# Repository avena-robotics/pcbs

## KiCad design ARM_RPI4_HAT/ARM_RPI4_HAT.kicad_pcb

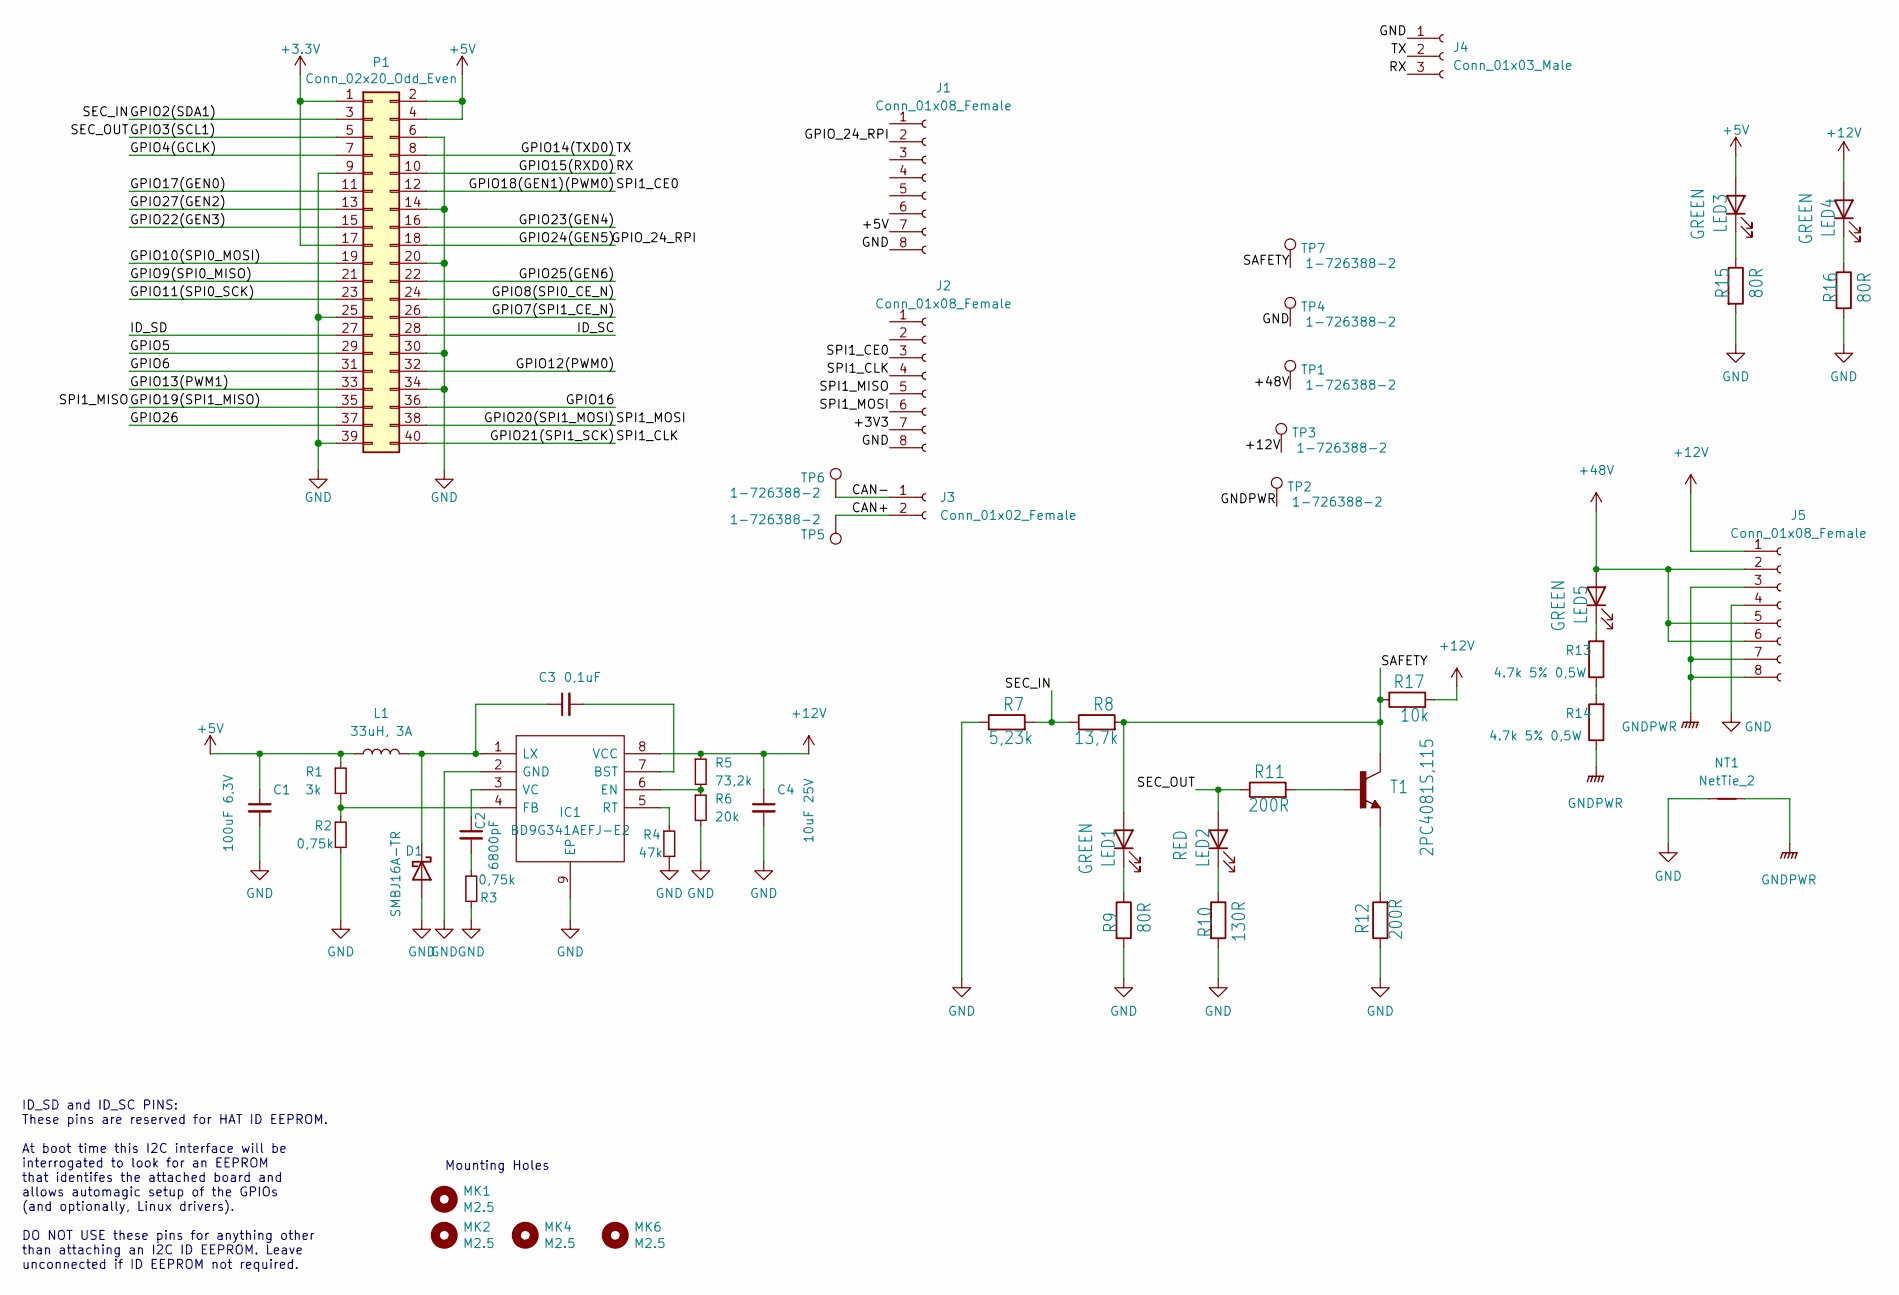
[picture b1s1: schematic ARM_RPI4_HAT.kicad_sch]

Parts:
C1: 100uF 6,3V; C_1206_3216Metric_Pad1.33x1.80mm_HandSolder
C2: 6800pF; C_0603_1608Metric_Pad1.08x0.95mm_HandSolder
C3: 0,1uF; C_0603_1608Metric_Pad1.08x0.95mm_HandSolder
C4: 10uF 25V; C_0603_1608Metric_Pad1.08x0.95mm_HandSolder
D1: SMBJ16A-TR; D_SMB_Handsoldering
IC1: BD9G341AEFJ-E2; SOIC127P600X100-9N; Mouser Part Number 755-BD9G341AEFJ-E2
J1, J2: Conn_01x08_Female; PinSocket_1x08_P2.54mm_Vertical
J3: Conn_01x02_Female; PinHeader_1x02_P2.54mm_Vertical
J4: Conn_01x03_Male; PinHeader_1x03_P2.54mm_Horizontal
J5: Conn_01x08_Female; 105314-2208
L1: 33uH, 3A; MPEV1D1040L330
LED1, LED3, LED4, LED5: GREEN; D_0603_1608Metric_Pad1.05x0.95mm_HandSolder
LED2: RED; D_0603_1608Metric_Pad1.05x0.95mm_HandSolder
MK1, MK2, MK4, MK6: M2.5; MountingHole_2.7mm_M2.5
NT1: NetTie_2; NetTie-2_SMD_Pad0.5mm
P1: Conn_02x20_Odd_Even; PinSocket_2x20_P2.54mm_Vertical
R1: 3k; R_0603_1608Metric_Pad0.98x0.95mm_HandSolder
R2, R3: 0,75k; R_0603_1608Metric_Pad0.98x0.95mm_HandSolder
R4: 47k; R_0603_1608Metric_Pad0.98x0.95mm_HandSolder
R5: 73,2k; R_0603_1608Metric_Pad0.98x0.95mm_HandSolder
R6: 20k; R_0603_1608Metric_Pad0.98x0.95mm_HandSolder
R7: 5,23k; R_0603_1608Metric_Pad0.98x0.95mm_HandSolder
R8: 13,7k; R_0603_1608Metric_Pad0.98x0.95mm_HandSolder
R9, R15, R16: 80R; R_0603_1608Metric_Pad0.98x0.95mm_HandSolder
R10: 130R; R_0603_1608Metric_Pad0.98x0.95mm_HandSolder
R11, R12: 200R; R_0603_1608Metric_Pad0.98x0.95mm_HandSolder
R13, R14: 4.7k 5% 0,5W; R_0805_2012Metric_Pad1.20x1.40mm_HandSolder
R17: 10k; R_0603_1608Metric_Pad0.98x0.95mm_HandSolder
T1: 2PC4081S,115; SOT23-EBC
TP1, TP2: 1-726388-2; 61-1537-11-0031
TP3, TP4, TP5, TP6, TP7: 1-726388-2; 61-1407-21-0031

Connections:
+5V: C1.1, J1.7, L1.1, LED3.2 (A), P1.2, P1.4, R1.1
+12V: C4.1, IC1.8 (VCC), J5.1, LED4.2 (A), R5.1, R17.2, TP3.1
+48V: J5.2, J5.5, J5.6, LED5.2 (A), TP1.1
/CAN+: J3.2, TP5.1
/CAN-: J3.1, TP6.1
/GPIO2(SDA1): P1.3, R7.2, R8.1
/GPIO3(SCL1): LED2.2 (A), P1.5, R11.1
/GPIO4(GCLK): P1.7
/GPIO5: P1.29
/GPIO6: P1.31
/GPIO7(SPI1_CE_N): P1.26
/GPIO8(SPI0_CE_N): P1.24
/GPIO9(SPI0_MISO): P1.21
/GPIO10(SPI0_MOSI): P1.19
/GPIO11(SPI0_SCK): P1.23
/GPIO12(PWM0): P1.32
/GPIO13(PWM1): P1.33
/GPIO14(TXD0): J4.2, P1.8
/GPIO15(RXD0): J4.3, P1.10
/GPIO16: P1.36
/GPIO17(GEN0): P1.11
/GPIO18(GEN1)(PWM0): J2.3, P1.12
/GPIO19(SPI1_MISO): J2.5, P1.35
/GPIO20(SPI1_MOSI): J2.6, P1.38
/GPIO21(SPI1_SCK): J2.4, P1.40
/GPIO22(GEN3): P1.15
/GPIO23(GEN4): P1.16
/GPIO24(GEN5): J1.2, P1.18
/GPIO25(GEN6): P1.22
/GPIO26: P1.37
/GPIO27(GEN2): P1.13
/ID_SC: P1.28
/ID_SD: P1.27
/SAFETY: LED1.2 (A), R8.2, R17.1, T1.C, TP7.1
GND: C1.2, C4.2, D1.2 (A), IC1.2 (GND), IC1.9 (EP), J1.8, J2.8, J4.1, J5.4, NT1.1, P1.6, P1.9, P1.14, P1.20, P1.25, P1.30, P1.34, P1.39, R2.2, R3.1, R4.2, R6.2, R7.1, R9.2, R10.2, R12.1, R15.2, R16.2, TP4.1
GNDPWR: J5.3, J5.7, J5.8, NT1.2, R14.1, TP2.1
unnamed: C2.1, IC1.3 (VC)
unnamed: C2.2, R3.2
unnamed: C3.1, D1.1 (K), IC1.1 (LX), L1.2
unnamed: C3.2, IC1.7 (BST)
unnamed: IC1.4 (FB), R1.2, R2.1
unnamed: IC1.5 (RT), R4.1
unnamed: IC1.6 (EN), R5.2, R6.1
unnamed: LED1.1 (K), R9.1
unnamed: LED2.1 (K), R10.1
unnamed: LED3.1 (K), R15.1
unnamed: LED4.1 (K), R16.1
unnamed: LED5.1 (K), R13.2
unnamed: R11.2, T1.B
unnamed: R12.2, T1.E
unnamed: R13.1, R14.2

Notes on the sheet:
ID_SD and ID_SC PINS: These pins are reserved for HAT ID EEPROM. At boot time this I2C interface will be interrogated to look for an EEPROM that identifes the attached board and allows automagic setup of the GPIOs (and optionally, Linux drivers). DO NOT USE these pins for anything other than attach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
Mounting Holes

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
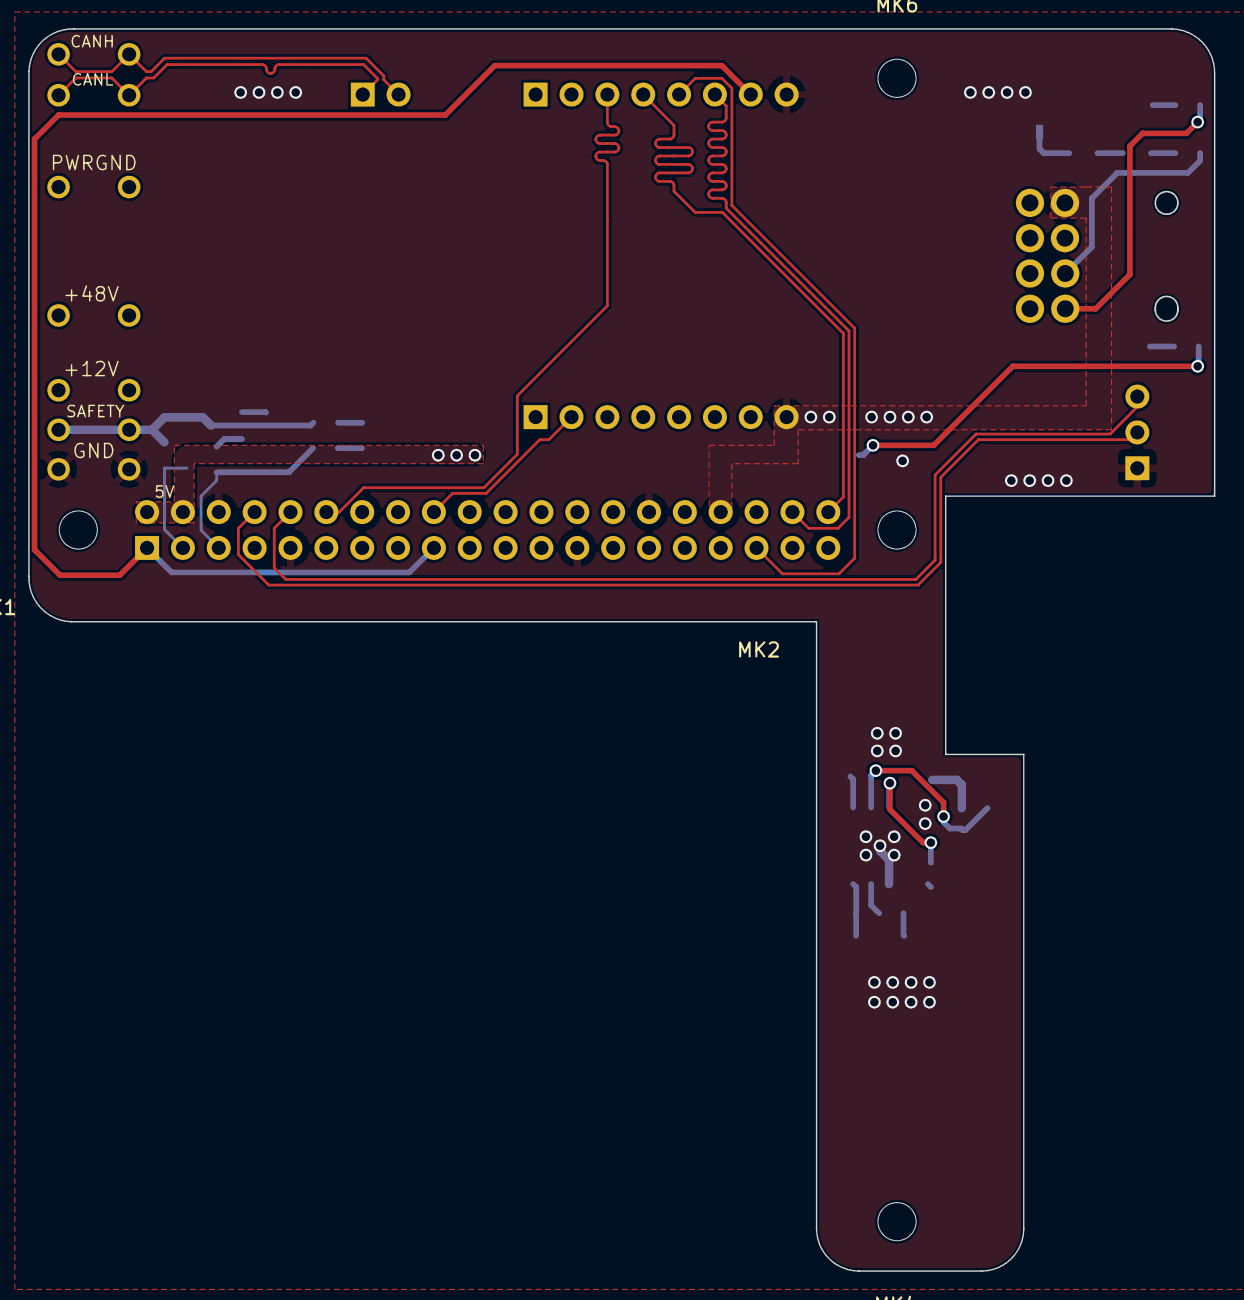
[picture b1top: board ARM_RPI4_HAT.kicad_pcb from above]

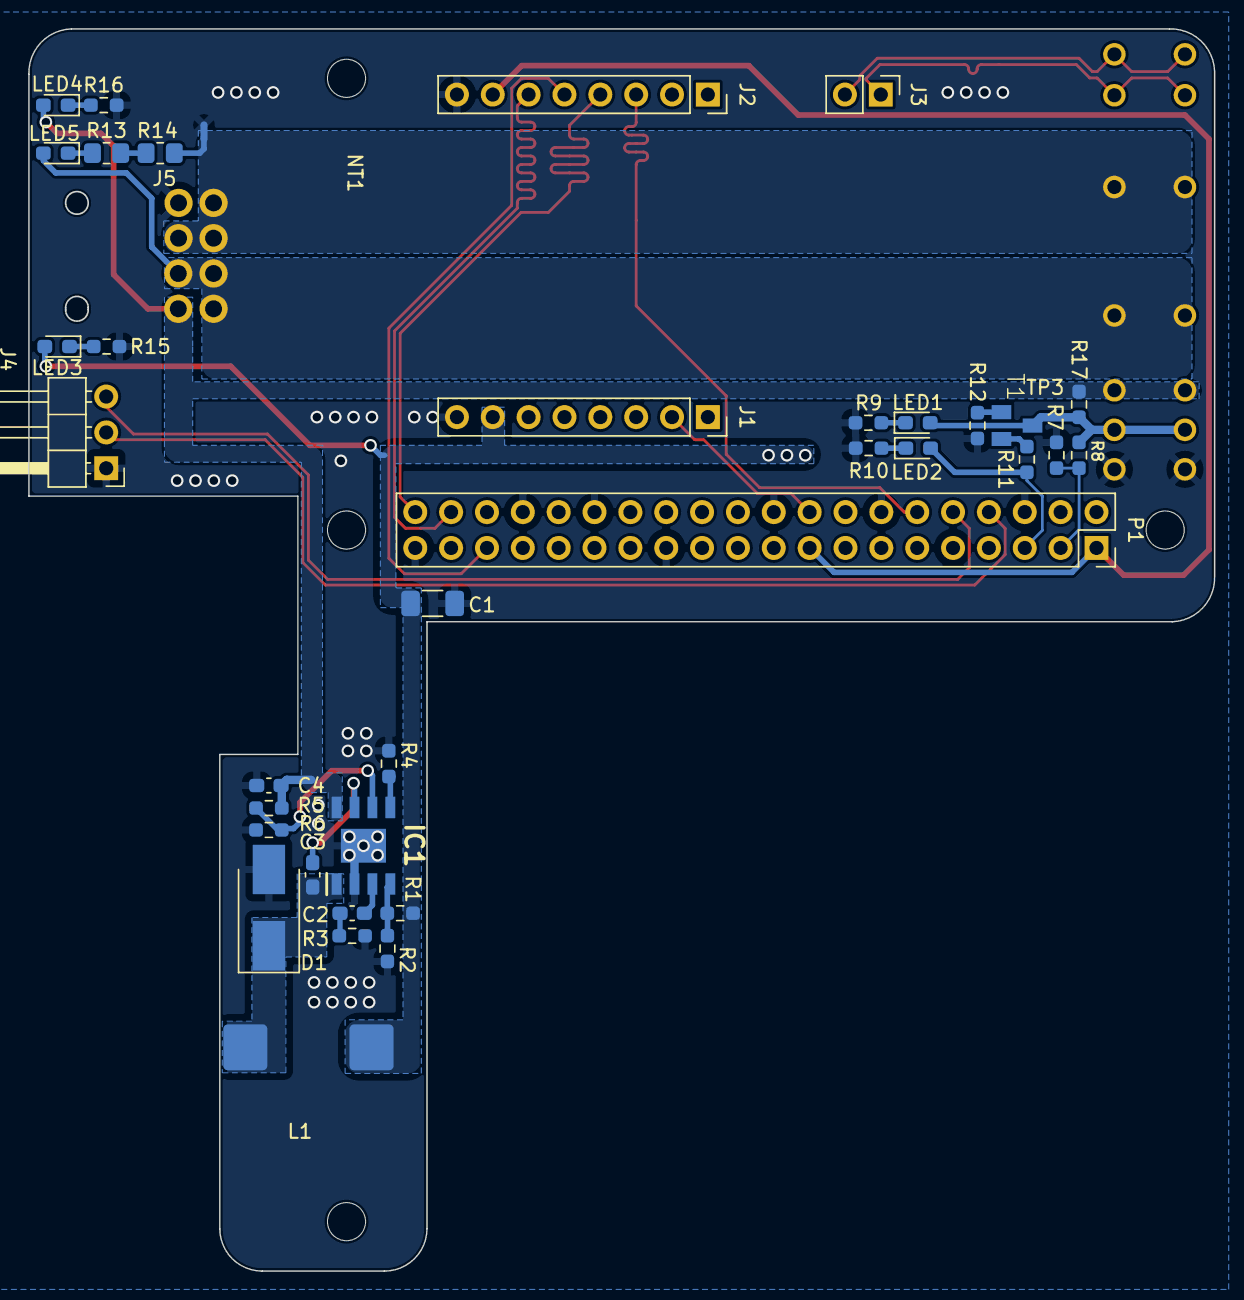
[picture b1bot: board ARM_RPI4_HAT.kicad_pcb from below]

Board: 2 copper layers, 84.0 x 88.0 mm, 48 parts (44 on the bottom side), 33 nets.

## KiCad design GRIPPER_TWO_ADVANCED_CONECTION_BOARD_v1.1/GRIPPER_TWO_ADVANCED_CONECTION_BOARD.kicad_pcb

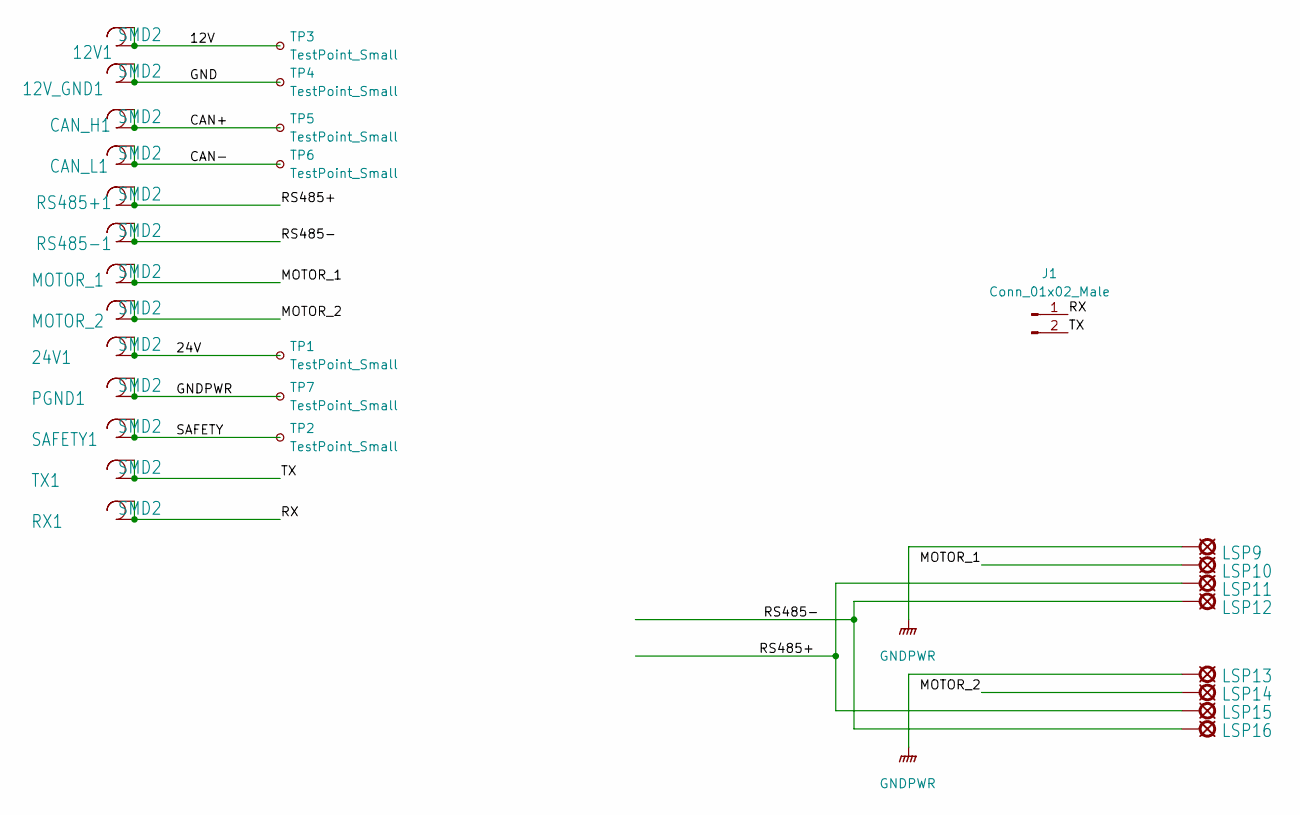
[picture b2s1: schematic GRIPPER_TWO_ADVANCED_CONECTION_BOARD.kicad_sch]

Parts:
12V1, 12V_GND1, 24V1: SMD2; SMD1,27-2,54
CAN_H1: SMD2; SMD1,27-2,54
CAN_L1: SMD2; SMD1,27-2,54
J1: Conn_01x02_Male; PinHeader_1x02_P2.54mm_Vertical
LSP9, LSP10, LSP11, LSP12, LSP13, LSP14, LSP15, LSP16: SE11
MOTOR_1, MOTOR_2: SMD2; SMD1,27-2,54
PGND1: SMD2; SMD1,27-2,54
RS485+1, RS485-1: SMD2; SMD1,27-2,54
RX1: SMD2; SMD1,27-2,54
SAFETY1: SMD2; SMD1,27-2,54
TP1, TP2, TP3, TP4, TP5, TP6, TP7: TestPoint_Small; TestPoint_Pad_1.0x1.0mm
TX1: SMD2; SMD1,27-2,54

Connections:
/12V: 12V1.1, 12V1.2, TP3.1
/24V: 24V1.1, 24V1.2, TP1.1
/CAN+: CAN_H1.1, CAN_H1.2, TP5.1
/CAN-: CAN_L1.1, CAN_L1.2, TP6.1
/GND: 12V_GND1.1, 12V_GND1.2, TP4.1
/MOTOR_1: LSP10.MP, MOTOR_1.1, MOTOR_1.2
/MOTOR_2: LSP14.MP, MOTOR_2.1, MOTOR_2.2
/RS485+: LSP11.MP, LSP15.MP, RS485+1.1, RS485+1.2
/RS485-: LSP12.MP, LSP16.MP, RS485-1.1, RS485-1.2
/RX: J1.1, RX1.1, RX1.2
/SAFETY: SAFETY1.1, SAFETY1.2, TP2.1
/TX: J1.2, TX1.1, TX1.2
GNDPWR: LSP9.MP, LSP13.MP, PGND1.1, PGND1.2, TP7.1

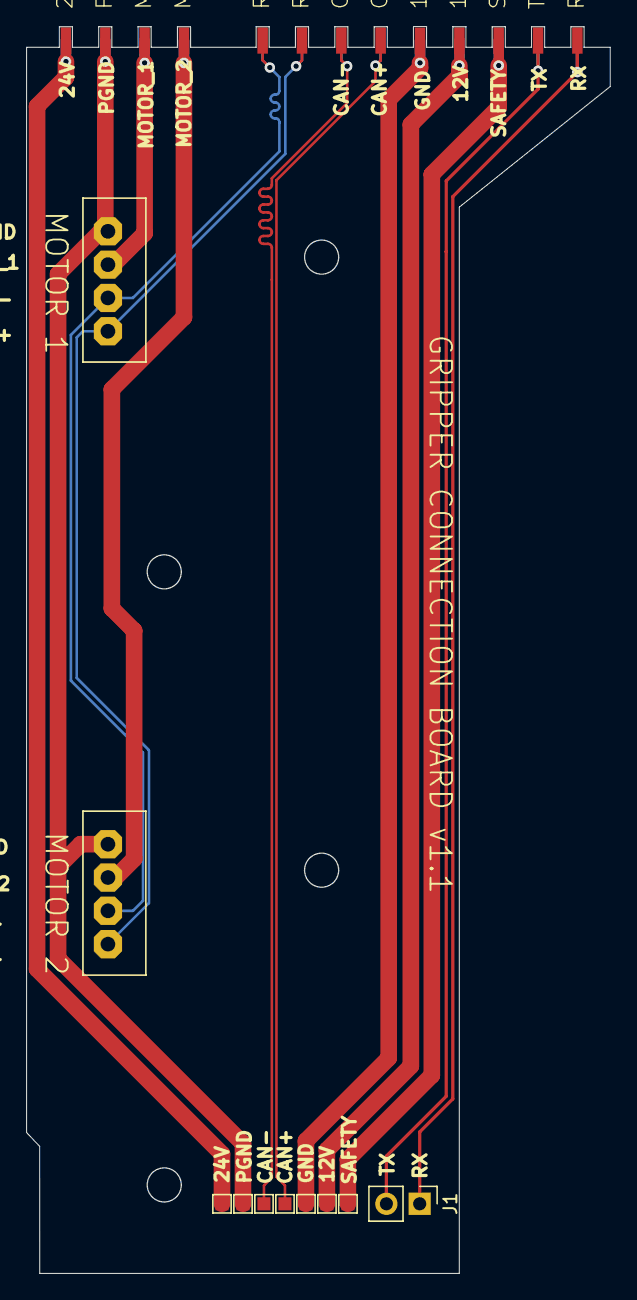
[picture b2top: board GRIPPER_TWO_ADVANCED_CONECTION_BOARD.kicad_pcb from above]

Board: 2 copper layers, 44.5 x 95.1 mm, 29 parts (0 on the bottom side), 13 nets.

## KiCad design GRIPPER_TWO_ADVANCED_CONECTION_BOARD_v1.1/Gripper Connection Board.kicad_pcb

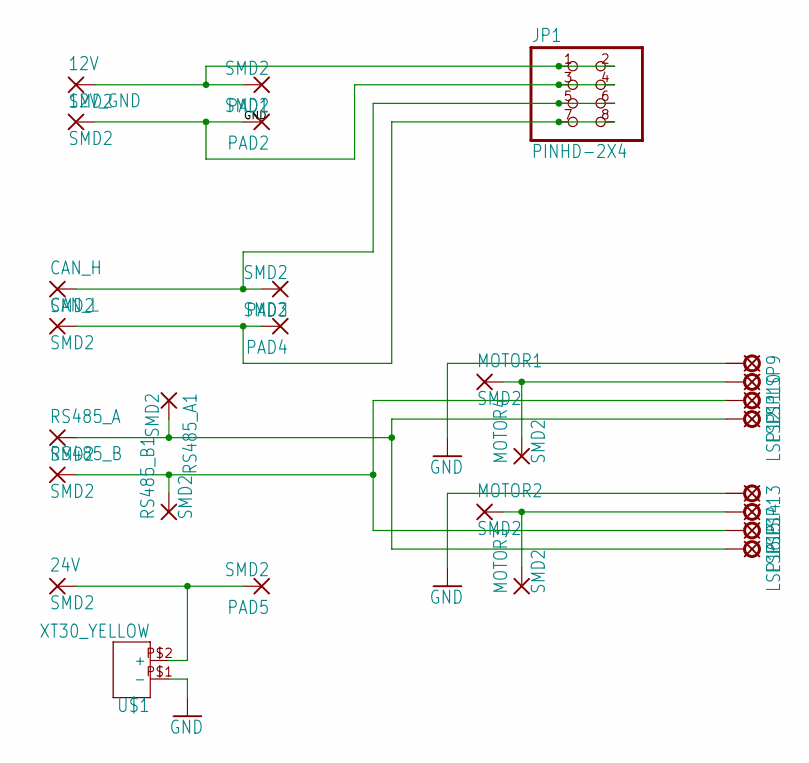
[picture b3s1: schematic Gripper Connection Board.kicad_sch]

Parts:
12V, 12V_GND, 24V: SMD2; SMD1,27-2,54
CAN_H: SMD2; SMD1,27-2,54
CAN_L: SMD2; SMD1,27-2,54
JP1: PINHD-2X4; 2X04
LSP9, LSP10, LSP11, LSP12, LSP13, LSP14, LSP15, LSP16: SE11
MOTOR1, MOTOR2, MOTOR3, MOTOR4: SMD2; SMD1,27-2,54
PAD1, PAD2, PAD3, PAD4, PAD5: SMD2; SMD1,27-2,54
RS485_A, RS485_A1, RS485_B, RS485_B1: SMD2; SMD1,27-2,54
U$1: XT30_YELLOW; XT30

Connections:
GND: 12V_GND.1, JP1.3, JP1.4, LSP9.MP, LSP13.MP, PAD2.1, U$1.P$1 (-)
unnamed: CAN_H.1, JP1.5, JP1.6, PAD3.1
unnamed: CAN_L.1, JP1.7, JP1.8, PAD4.1
unnamed: 12V.1, JP1.1, JP1.2, PAD1.1
unnamed: 24V.1, PAD5.1, U$1.P$2 (+)
unnamed: LSP11.MP, LSP15.MP, RS485_B.1, RS485_B1.1
unnamed: LSP12.MP, LSP16.MP, RS485_A.1, RS485_A1.1
unnamed: LSP10.MP, MOTOR1.1, MOTOR4.1
unnamed: LSP14.MP, MOTOR2.1, MOTOR3.1

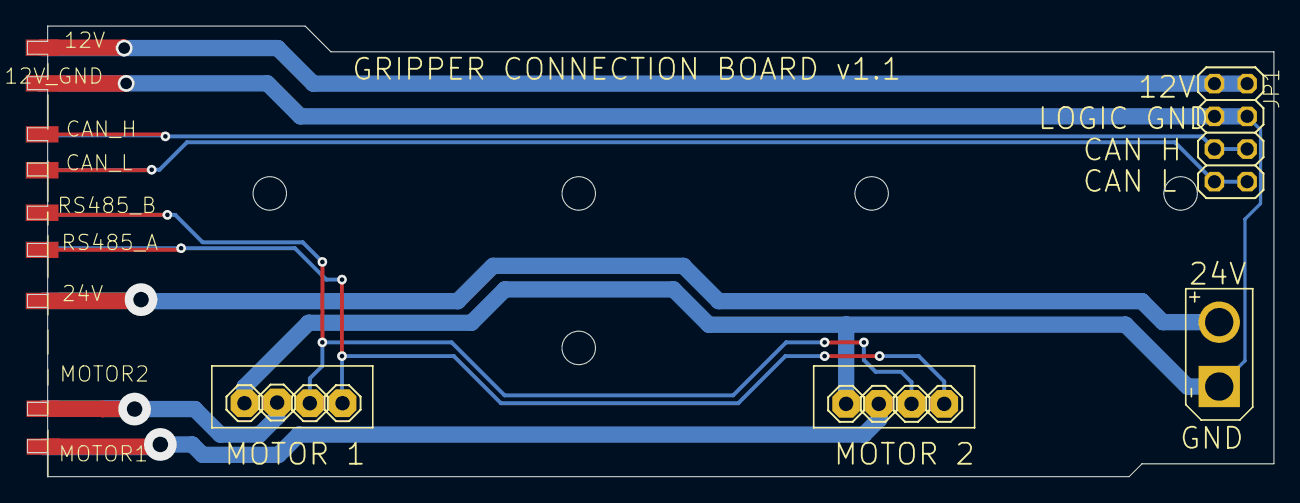
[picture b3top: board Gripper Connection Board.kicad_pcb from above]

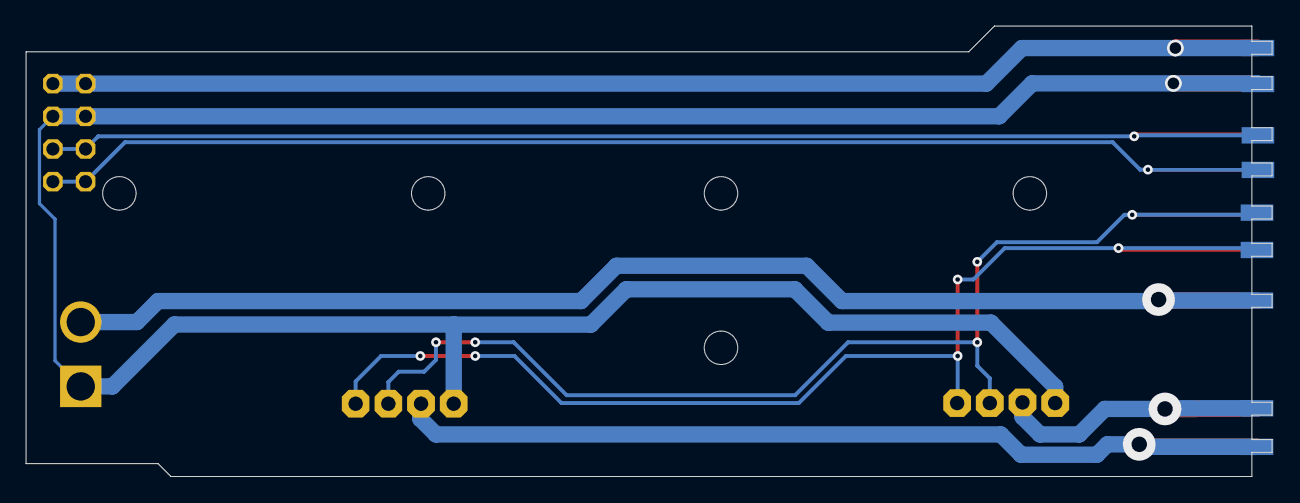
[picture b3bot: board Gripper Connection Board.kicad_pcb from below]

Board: 2 copper layers, 96.8 x 35.0 mm, 28 parts (9 on the bottom side), 9 nets.

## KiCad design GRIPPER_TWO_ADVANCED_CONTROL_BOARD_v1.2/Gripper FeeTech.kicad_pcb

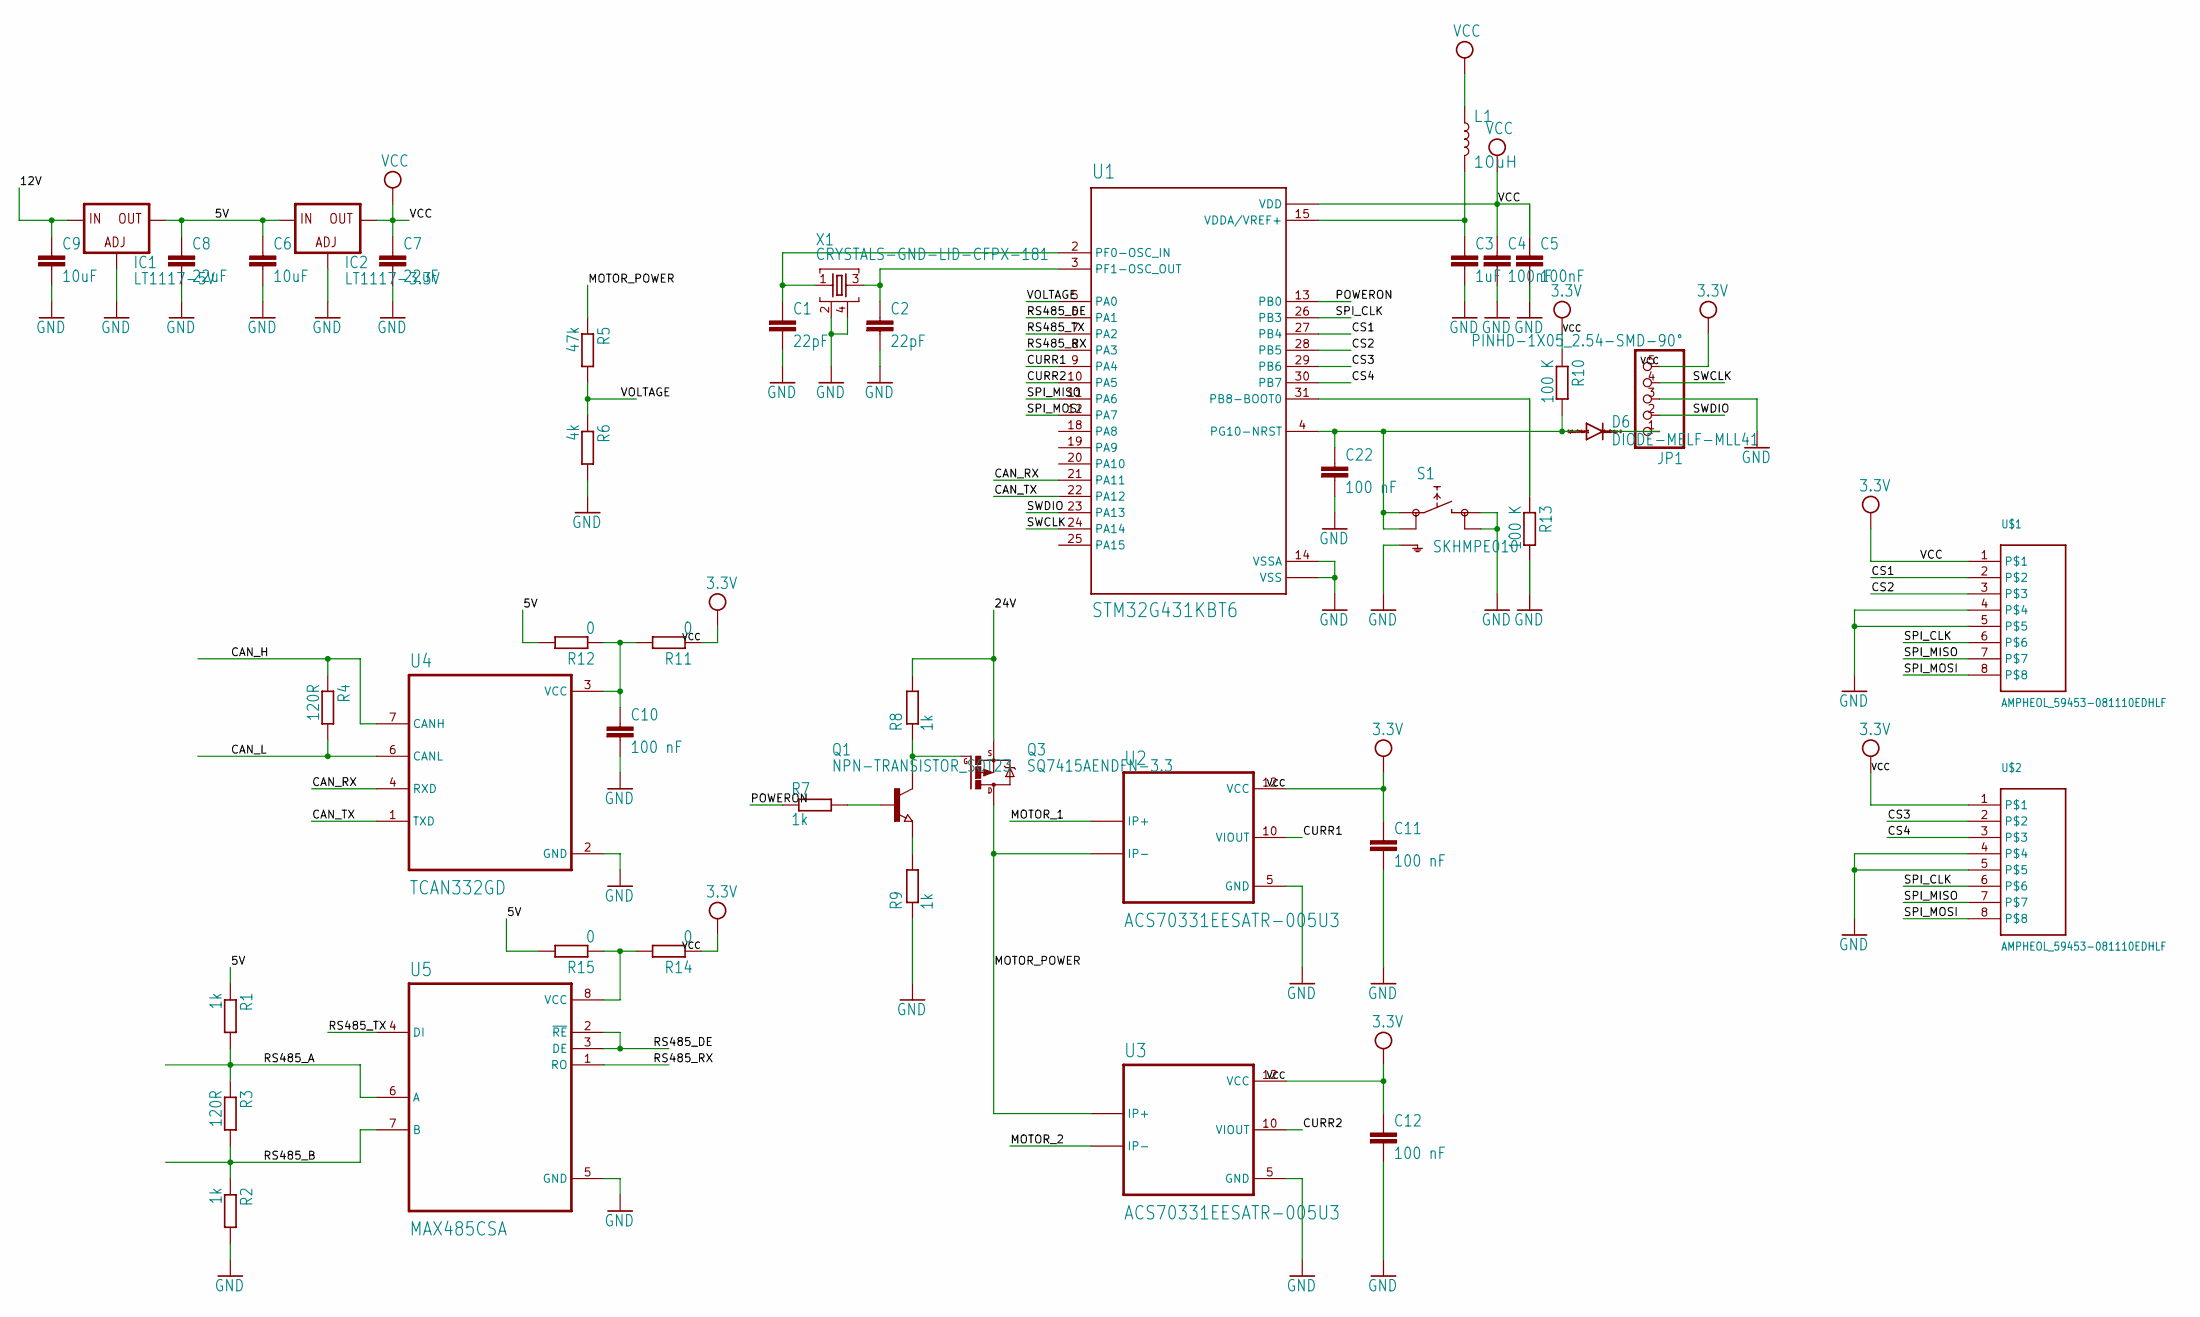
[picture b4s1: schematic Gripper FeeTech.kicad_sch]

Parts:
C1, C2: 22pF; C0402
C3: 1uF; C0402
C4, C5: 100nF; C0402
C6, C9: 10uF; C0402
C7, C8: 22uF; C0402
C10, C11, C12, C22: 100 nF; C0402
D6: DIODE-MELF-MLL41; MELF-MLL41
IC1: LT1117-5V; SOT223
IC2: LT1117-3.3V; SOT223
JP1: PINHD-1X05_2.54-SMD-90°; 1X05SMD_90
L1: 10uH; 0603
Q1: NPN-TRANSISTOR_SOT23; SOT23
Q3: SQ7415AENDFN-3.3; DFN3.3X3.3
R1, R2, R7, R8, R9: 1k; R0402
R3, R4: 120R; R0402
R5: 47k; R0402
R6: 4k; R0402
R10, R13: 100 K; R0402
R11, R12, R14, R15: 0; R0402
S1: SKHMPE010; SKHMPXE010
U1: STM32G431KBT6; QFP80P900X900X160-32N
U2, U3: ACS70331EESATR-005U3; ALLEGRO_ACS70331EESATR-005U3
U4: TCAN332GD; SOIC127P599X175-8N
U5: MAX485CSA; SOIC127P600X175-8N
U$1, U$2: AMPHEOL_59453-081110EDHLF; AMPHENOL_59453_8PIN
X1: CRYSTALS-GND-LID-CFPX-181; 2.5X2-4-PAD

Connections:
5V: C6.1, C8.1, IC1.4 (OUT), IC2.3 (IN), R1.1, R12.2, R15.2
12V: C9.1, IC1.3 (IN)
24V: Q3.1 (S), Q3.2 (S), Q3.3 (S), R8.2
CAN_H: R4.1, U4.7 (CANH)
CAN_L: R4.2, U4.6 (CANL)
CAN_RX: U1.21 (PA11), U4.4 (RXD)
CAN_TX: U1.22 (PA12), U4.1 (TXD)
CS1: U1.27 (PB4), U$1.2
CS2: U1.28 (PB5), U$1.3
CS3: U1.29 (PB6), U$2.2
CS4: U1.30 (PB7), U$2.3
CURR1: U1.9 (PA4), U2.10 (VIOUT)
CURR2: U1.10 (PA5), U3.10 (VIOUT)
GND: C1.2, C2.2, C3.2, C4.2, C5.2, C6.2, C7.2, C8.2, C9.2, C10.2, C11.2, C12.2, C22.2, IC1.1 (ADJ), IC2.1 (ADJ), JP1.3, R2.2, R6.2, R9.1, R13.2, S1.3 (2.1), S1.4 (2.2), S1.5 (SH), U1.14 (VSSA), U1.16 (VSS), U1.32 (VSS), U2.5 (GND), U3.5 (GND), U4.2 (GND), U5.5 (GND), U$1.4, U$1.5, U$2.4, U$2.5, X1.2, X1.4
MOTOR_1: U2.1 (IP+), U2.2 (IP+)
MOTOR_2: U3.3 (IP-), U3.4 (IP-)
MOTOR_POWER: Q3.5 (D), Q3.6 (D), Q3.7 (D), Q3.8 (D), R5.1, U2.3 (IP-), U2.4 (IP-), U3.1 (IP+), U3.2 (IP+)
unnamed: C2.1, U1.3 (PF1-OSC_OUT), X1.3
unnamed: C1.1, U1.2 (PF0-OSC_IN), X1.1
unnamed: C3.1, L1.2, U1.15 (VDDA/VREF+)
unnamed: C22.1, D6.A, R10.2, S1.1 (1.1), S1.2 (1.2), U1.4 (PG10-NRST)
unnamed: Q1.1 (B), R7.2
unnamed: Q1.3 (C), Q3.4 (G), R8.1
unnamed: Q1.2 (E), R9.2
unnamed: R14.2, R15.1, U5.8 (VCC)
unnamed: C10.1, R11.2, R12.1, U4.3 (VCC)
unnamed: R13.1, U1.31 (PB8-BOOT0)
POWERON: R7.1, U1.13 (PB0)
RESET: D6.C, JP1.1
RS485_A: R1.2, R3.1, U5.6 (A)
RS485_B: R2.1, R3.2, U5.7 (B)
RS485_DE: U1.6 (PA1), U5.2 (~RE), U5.3 (DE)
RS485_RX: U1.8 (PA3), U5.1 (RO)
RS485_TX: U1.7 (PA2), U5.4 (DI)
SPI_CLK: U1.26 (PB3), U$1.6, U$2.6
SPI_MISO: U1.11 (PA6), U$1.7, U$2.7
SPI_MOSI: U1.12 (PA7), U$1.8, U$2.8
SWCLK: JP1.4, U1.24 (PA14)
SWDIO: JP1.2, U1.23 (PA13)
VCC: C4.1, C5.1, C7.1, C11.1, C12.1, IC2.4 (OUT), JP1.5, L1.1, R10.1, R11.1, R14.1, U1.1 (VDD), U1.17 (VDD), U2.12 (VCC), U3.12 (VCC), U$1.1, U$2.1
VOLTAGE: R5.2, R6.1, U1.5 (PA0)

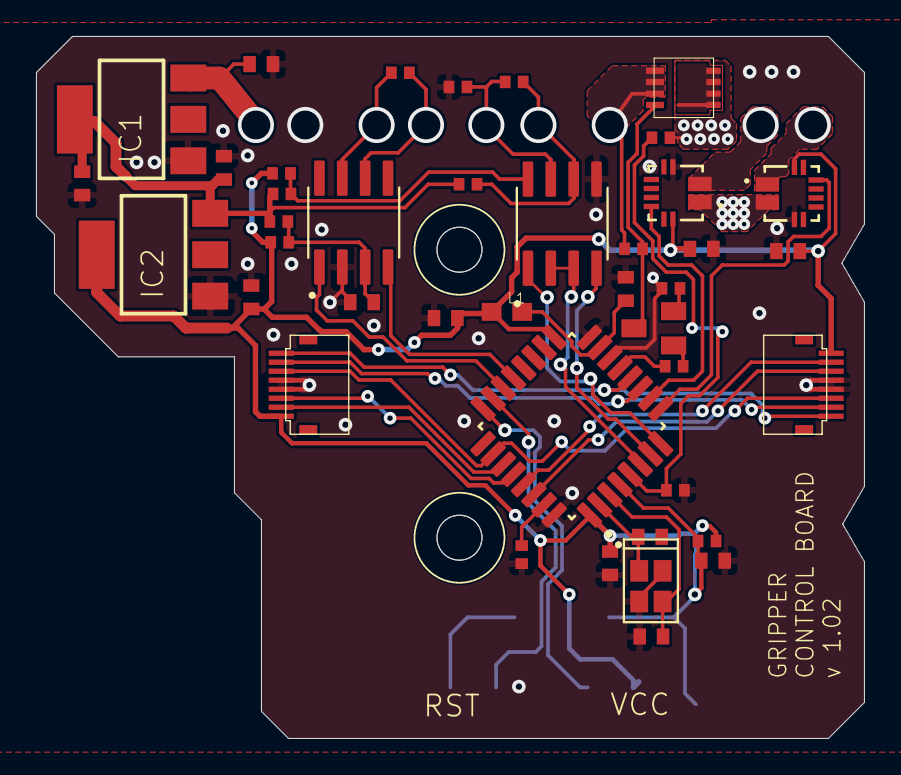
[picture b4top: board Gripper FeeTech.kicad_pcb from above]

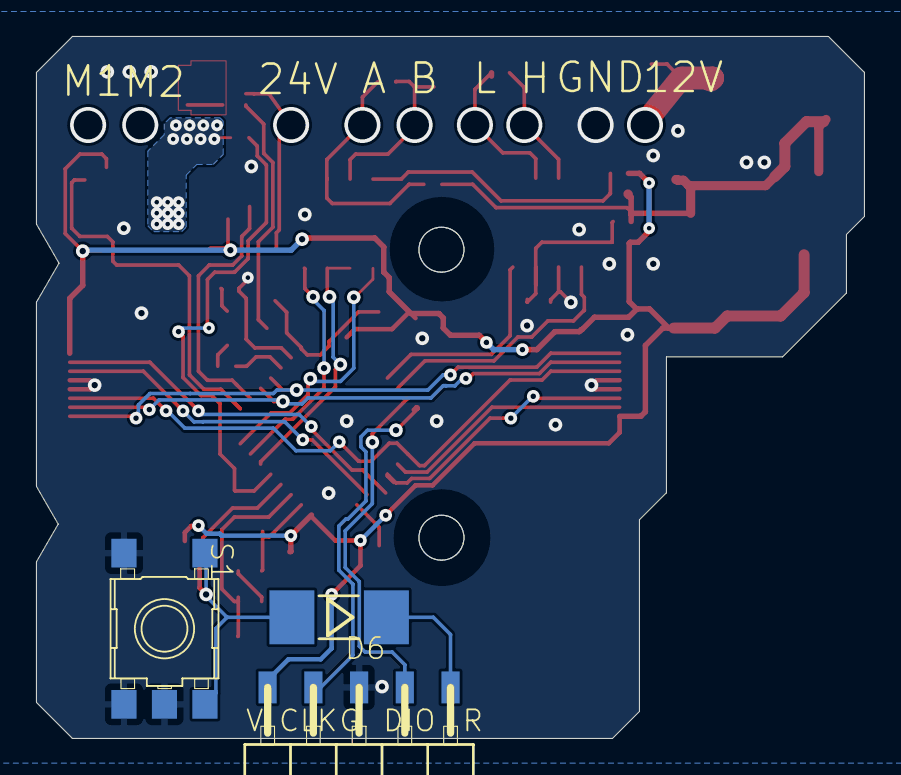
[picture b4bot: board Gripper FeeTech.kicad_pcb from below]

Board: 2 copper layers, 46.0 x 39.0 mm, 46 parts (3 on the bottom side), 41 nets.

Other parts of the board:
@HOLE0, @HOLE1: (no value)

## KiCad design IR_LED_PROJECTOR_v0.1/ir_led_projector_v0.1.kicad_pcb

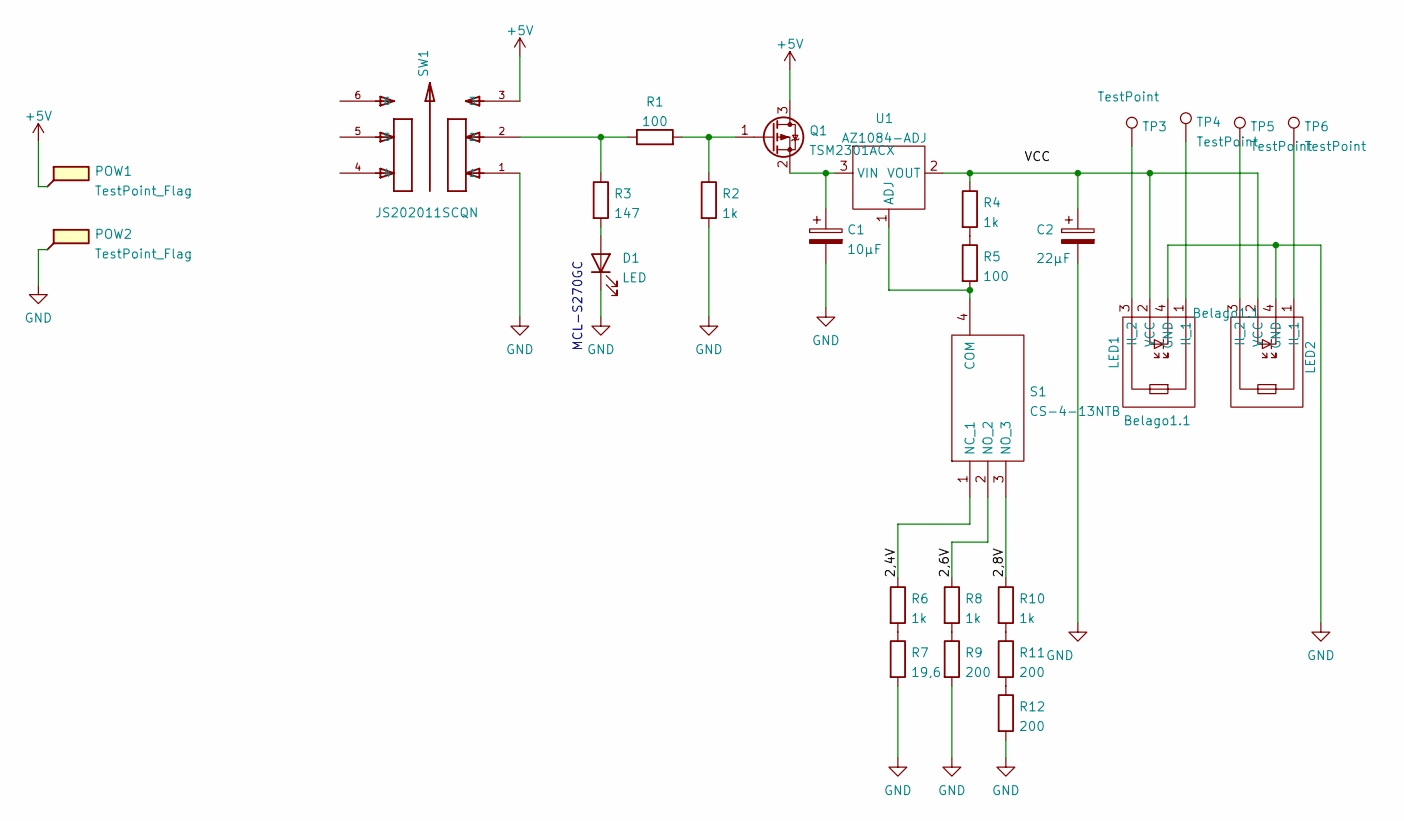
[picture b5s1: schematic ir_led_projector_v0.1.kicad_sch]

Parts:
C1: 10µF; C_Elec_4x5.4
C2: 22µF; C_Elec_4x5.4
D1: LED; D_0805_2012Metric_Pad1.15x1.40mm_HandSolder
LED1, LED2: Belago1.1
POW1, POW2: TestPoint_Flag; TestPoint_Pad_4.0x4.0mm
Q1: TSM2301ACX; SOT-23
R1, R5: 100; R_0805_2012Metric_Pad1.20x1.40mm_HandSolder
R2, R4, R6, R8, R10: 1k; R_0805_2012Metric_Pad1.20x1.40mm_HandSolder
R3: 147; R_0805_2012Metric_Pad1.20x1.40mm_HandSolder
R7: 19,6; R_0805_2012Metric_Pad1.20x1.40mm_HandSolder
R9, R11, R12: 200; R_0805_2012Metric_Pad1.20x1.40mm_HandSolder
S1: CS-4-13NTB; CS413NTB; Manufacturer_Part_Number CS-4-13NTB
SW1: JS202011SCQN; SW_JS202011SCQN
TP3, TP4, TP5, TP6: TestPoint; TestPoint_Pad_1.0x1.0mm
U1: AZ1084-ADJ; TO-252-3_TabPin2

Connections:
+5V: POW1.1, Q1.3 (D), SW1.3
/2,4V: R6.1, S1.1 (NC_1)
/2,6V: R8.1, S1.2 (NO_2)
/2,8V: R10.1, S1.3 (NO_3)
GND: C1.2, C2.2, D1.1 (K), LED1.4 (GND), LED2.4 (GND), POW2.1, R2.2, R7.2, R9.2, R12.2, SW1.1
unnamed: C1.1, Q1.2 (S), U1.3 (VIN)
unnamed: C2.1, LED1.2 (VCC), LED2.2 (VCC), R4.1, U1.2 (VOUT)
unnamed: D1.2 (A), R3.2
unnamed: LED1.1 (Il_1), TP4.1
unnamed: LED1.3 (Il_2), TP3.1
unnamed: LED2.1 (Il_1), TP6.1
unnamed: LED2.3 (Il_2), TP5.1
unnamed: Q1.1 (G), R1.2, R2.1
unnamed: R1.1, R3.1, SW1.2
unnamed: R4.2, R5.1
unnamed: R5.2, S1.4 (COM), U1.1 (ADJ)
unnamed: R6.2, R7.1
unnamed: R8.2, R9.1
unnamed: R10.2, R11.1
unnamed: R11.2, R12.1

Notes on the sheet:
MCL-S270GC

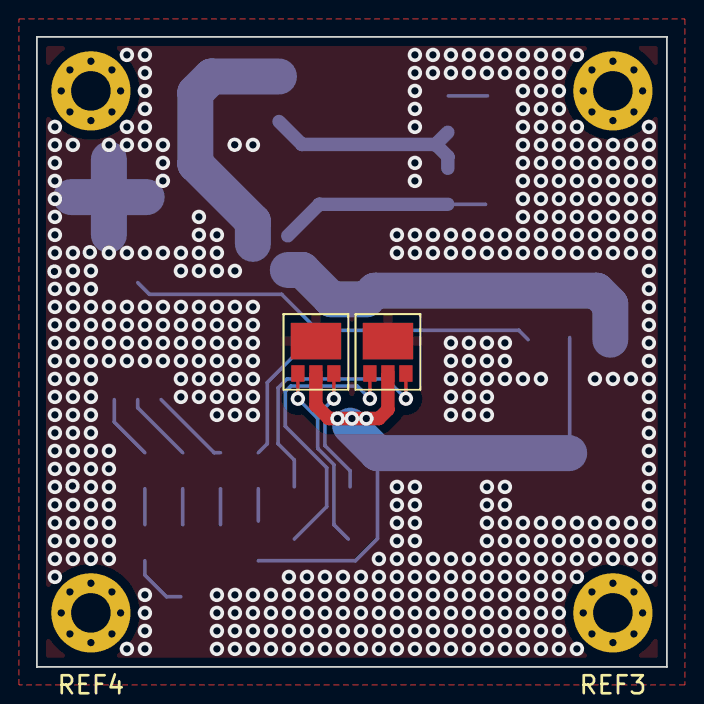
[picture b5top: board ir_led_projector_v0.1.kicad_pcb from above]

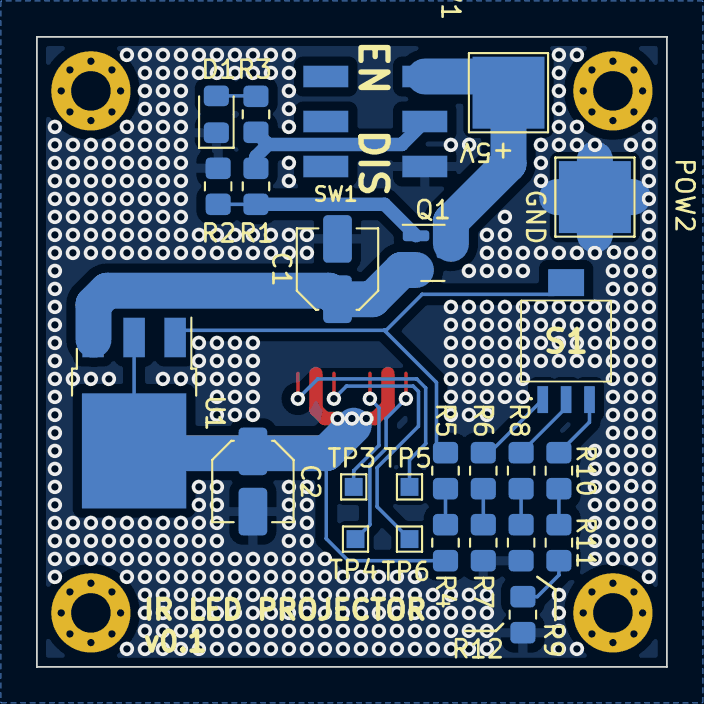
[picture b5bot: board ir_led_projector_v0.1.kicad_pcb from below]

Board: 2 copper layers, 35.0 x 35.0 mm, 31 parts (25 on the bottom side), 20 nets.

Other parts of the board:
REF1, REF2, REF3, REF4: MountingHole_2.2mm_M2_Pad_Via
